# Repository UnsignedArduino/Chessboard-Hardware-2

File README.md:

[Chessboard-Hardware](https://github.com/UnsignedArduino/Chessboard-Hardware) |
[Chessboard-Hardware-2](https://github.com/UnsignedArduino/Chessboard-Hardware-2) |
[Chessboard-Design](https://github.com/UnsignedArduino/Chessboard-Design) |
[Chessboard-Nano](https://github.com/UnsignedArduino/Chessboard-Nano) |
[Chessboard-Pi](https://github.com/UnsignedArduino/Chessboard-Pi)

# Chessboard-Hardware-2

Hardware for a magnetic-piece-tracking digital chessboard! WIP

This repository contains the KiCad PCB project for the rest of the Chessboard's wiring.

## Notes

### Models

All models were modified in Fusion 360. 

* Raspberry Pi Zero WH was modified from [Julian's model](https://grabcad.com/library/raspberry-pi-zero-w-1)
  and combined with `${KICAD8_3DMODEL_DIR}/Connector_PinSocket_2.54mm.3dshapes/PinSocket_2x20_P2.54mm_Vertical.step`
  from the KiCad 3D model library.

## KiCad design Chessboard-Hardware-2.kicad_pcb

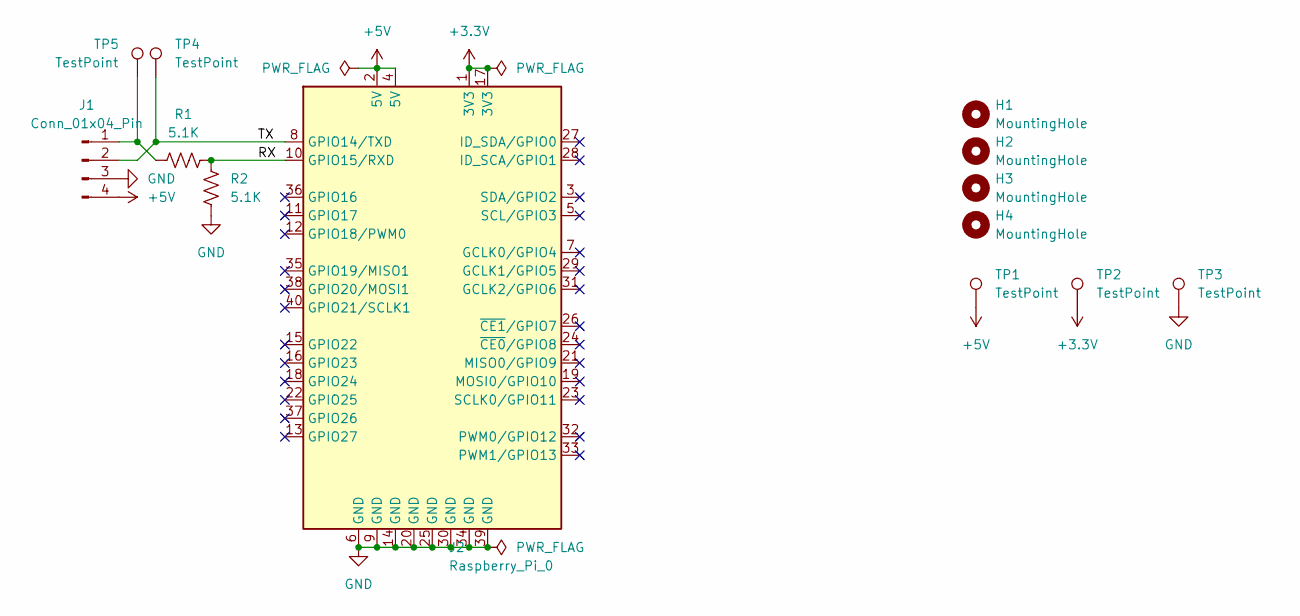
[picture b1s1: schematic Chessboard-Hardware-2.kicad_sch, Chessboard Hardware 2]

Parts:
H1, H2, H3, H4: MountingHole; MountingHole_2.7mm_M2.5
J1: Conn_01x04_Pin; JST_XH_B4B-XH-A_1x04_P2.50mm_Vertical
J2: Raspberry_Pi_0; Raspberry_Pi_Zero_Socketed_THT_FaceDown_MountingHoles
R1, R2: 5.1K; R_Axial_DIN0309_L9.0mm_D3.2mm_P12.70mm_Horizontal
TP1, TP2, TP3, TP4, TP5: TestPoint; PinHeader_1x01_P2.54mm_Vertical

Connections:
+3.3V: J2.1 (3V3), J2.17 (3V3), TP2.1
+5V: J1.4, J2.2 (5V), J2.4 (5V), TP1.1
/RX: J2.10 (GPIO15/RXD), R1.2, R2.2
/TX: J1.2, J2.8 (GPIO14/TXD), TP4.1
GND: J1.3, J2.6 (GND), J2.9 (GND), J2.14 (GND), J2.20 (GND), J2.25 (GND), J2.30 (GND), J2.34 (GND), J2.39 (GND), R2.1, TP3.1
unnamed: J1.1, R1.1, TP5.1

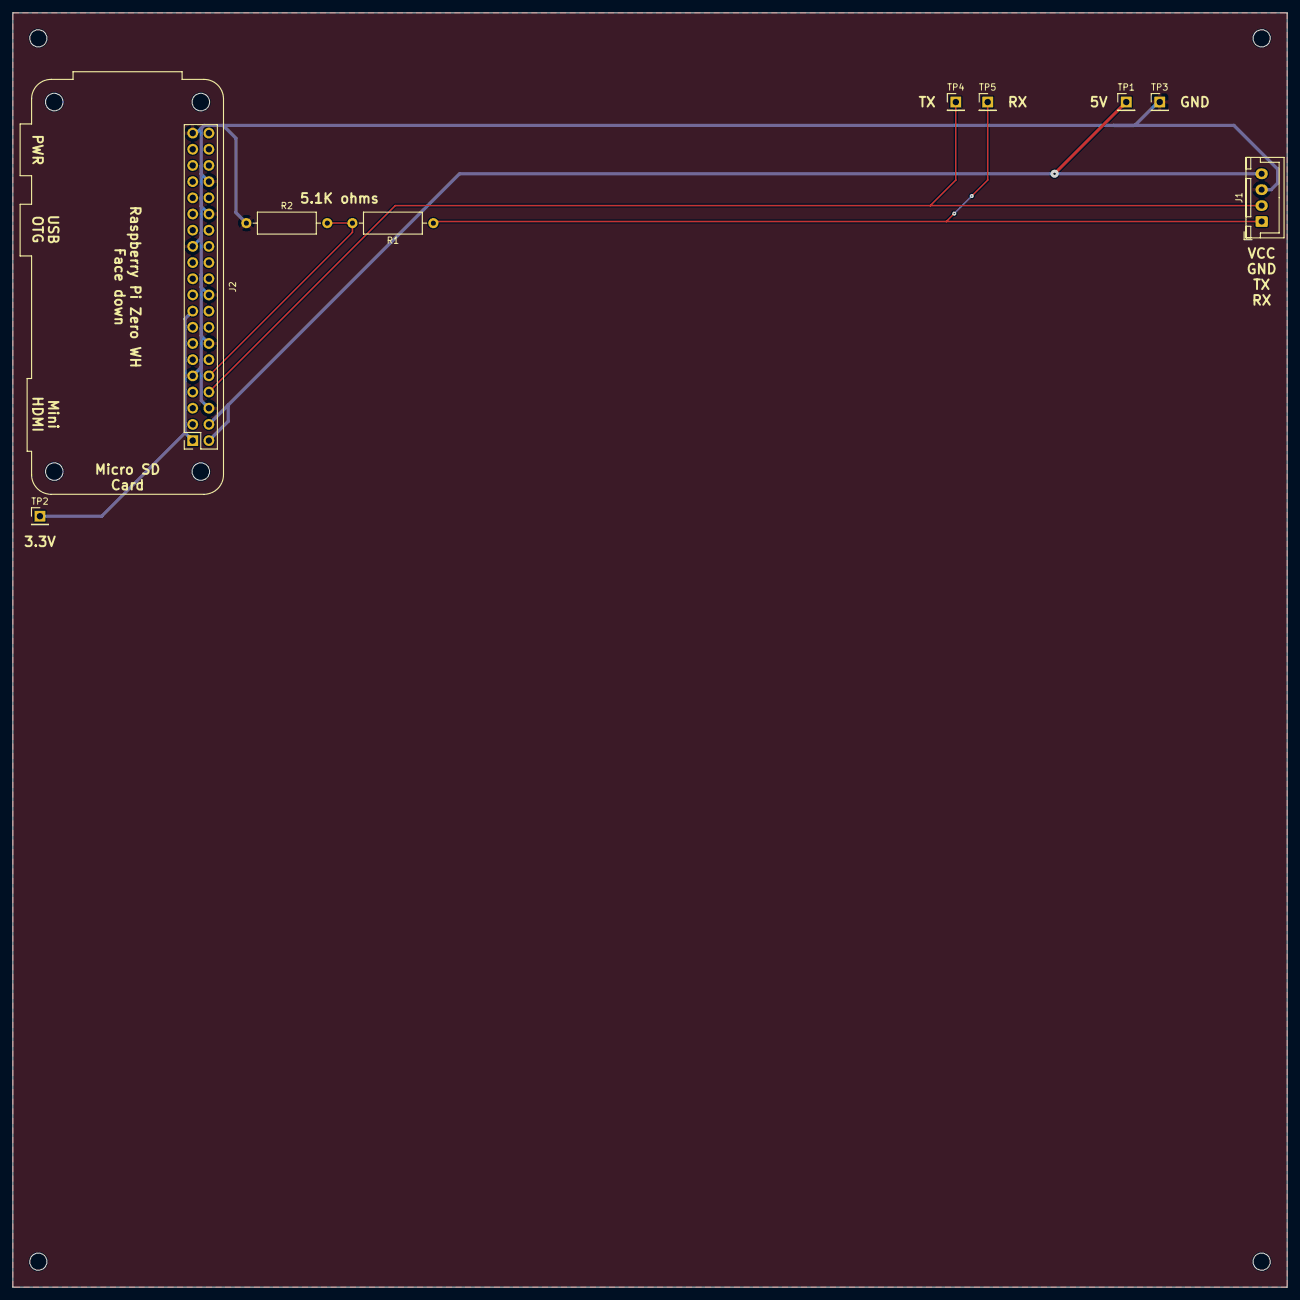
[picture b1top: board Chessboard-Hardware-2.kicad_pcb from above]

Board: 2 copper layers, 200.0 x 200.0 mm, 13 parts (0 on the bottom side), 6 nets.

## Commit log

2025-04-13 RPi Zero template
2025-04-13 Setup for chessboard layout
2025-04-13 Add model for Raspberry_Pi_Zero_Socketed_THT_FaceDown_MountingHoles
2025-04-14 Add JST-XH connector and schematic
2025-04-14 Schematic and PCB for wiring up Pi to Nano
2025-04-14 Add test points
2025-04-14 Update RPi Zero model
2025-04-14 Shift serial JST-XH connector over for space
